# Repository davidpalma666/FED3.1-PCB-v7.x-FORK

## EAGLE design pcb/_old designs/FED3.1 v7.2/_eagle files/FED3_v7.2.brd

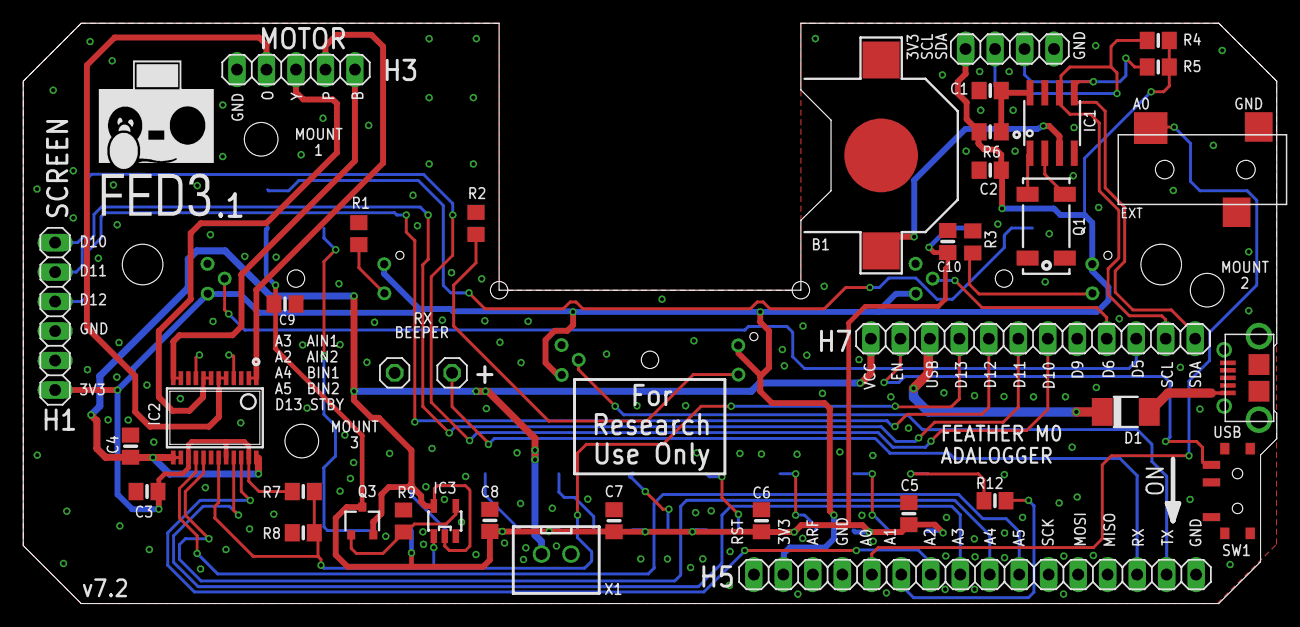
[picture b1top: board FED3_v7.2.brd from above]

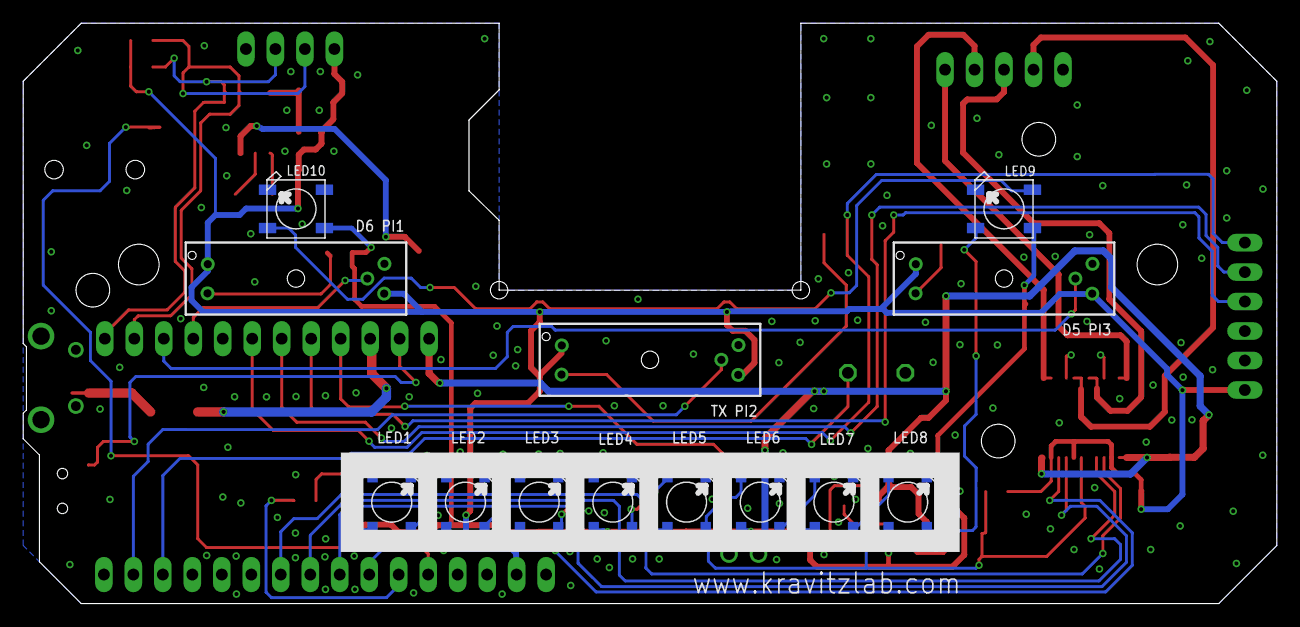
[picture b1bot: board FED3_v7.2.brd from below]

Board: 2 copper layers, 108.0 x 50.0 mm, 51 parts (13 on the bottom side), 45 nets.

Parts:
AUX_I2C: 1X04
B1: CR1220
BEEP1, BEEP2: 1X01
C1, C2, C5, C6, C7, C8, C9, C10: 10uF; 0805-NO
C3, C4: 10µF; 0805-NO
D1: DO-214AC
EXT: 35RASMT2BHNTRX
FEATHER_L: 1X16
FEATHER_R: 1X12
IC1: RTC_PCF8523T; SOIC8_150MIL
IC2: TB6612 SSOP; SSOP24
IC3: M74VHC1GT50DTT1G; SOT23-5
LED1, LED2, LED3, LED4, LED5, LED6, LED7, LED8, LED9, LED10: WS2812B5050; WS2812B
MOTOR: 1X05
PI1, PI2, PI3: GP1A57HR
Q1: 32.768; CRYSTAL_8X3.8
Q3: TSMT3
R1, R2, R3: 1k; R0805
R4, R5: 4K7; 0805-NO
R6: 1K; 0805-NO
R7: DNI; 0805-NO
R8: 4k7; 0805-NO
R9: 37k; R0805
R12: 470; 0805-NO
SCREEN: 1X06
SW1: SSSS811101
USB: USB_MICRO_B; ZX62D-B-5P8
X1: B2B-PH-K-S(LF)(SN); JST-XH-02-PACKAGE-ROUND-PAD

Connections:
3V3: AUX_I2C.1, C2.1, C3.1, FEATHER_L.2, IC2.15, IC2.20, IC2.23, PI1.1, PI1.3, PI2.1, PI2.3, PI3.1, PI3.3, R4.1, R5.2, R6.1, R7.2, SCREEN.6
A0: EXT.4, FEATHER_L.5
A1: FEATHER_L.6, R12.2
A2: FEATHER_L.7, IC2.22
A3: FEATHER_L.8, IC2.21
A4: FEATHER_L.9, IC2.17
A5: FEATHER_L.10, IC2.16
BLUE: IC2.11, IC2.12, MOTOR.5
D5: FEATHER_R.10, PI3.4
D6: FEATHER_R.9, PI1.4
D10: FEATHER_R.7, SCREEN.1
D11: FEATHER_R.6, SCREEN.2
D12: FEATHER_R.5, SCREEN.3
D13: FEATHER_R.4, IC2.19, IC3.1, R7.1, R8.2
EN: FEATHER_R.2, SW1.3
GND: AUX_I2C.4, B1.-, BEEP2.1, C1.2, C2.2, C3.2, C4.2, C5.2, C6.2, C7.2, C8.2, C9.2, C10.2, EXT.5, FEATHER_L.4, FEATHER_L.16, IC1.4, IC2.3, IC2.4, IC2.9, IC2.10, IC2.18, IC3.3, LED1.3-GND, LED2.3-GND, LED3.3-GND, LED4.3-GND, LED5.3-GND, LED6.3-GND, LED7.3-GND, LED8.3-GND, LED9.3-GND, LED10.3-GND, MOTOR.1, PI1.5, PI2.5, PI3.5, R1.2, R2.2, R3.2, R8.1, R9.1, SCREEN.4, SW1.2, USB.P$5, X1.1
unnamed: PI2.2, R2.1
unnamed: PI3.2, R1.1
unnamed: PI1.2, R3.1
unnamed: D1.A, USB.P$1
unnamed: LED1.2-DOUT, LED2.4-DIN
unnamed: C1.1, IC1.8, R6.2
unnamed: LED2.2-DOUT, LED3.4-DIN
unnamed: LED3.2-DOUT, LED4.4-DIN
unnamed: LED4.2-DOUT, LED5.4-DIN
unnamed: LED5.2-DOUT, LED6.4-DIN
unnamed: LED6.2-DOUT, LED7.4-DIN
unnamed: LED7.2-DOUT, LED8.4-DIN
unnamed: IC1.1, Q1.P$1
unnamed: IC1.2, Q1.P$4
unnamed: LED1.4-DIN, R12.1
unnamed: LED9.2-DOUT, LED10.4-DIN
unnamed: LED8.2-DOUT, LED9.4-DIN
ORANGE: IC2.5, IC2.6, MOTOR.2
OUT3: IC3.4, Q3.P$1, R9.2
PINK: IC2.1, IC2.2, MOTOR.4
RX: BEEP1.1, FEATHER_L.14
SCL: AUX_I2C.2, FEATHER_R.11, IC1.6, R4.2
SDA: AUX_I2C.3, FEATHER_R.12, IC1.5, R5.1
TX: FEATHER_L.15, PI2.4
USB: D1.C, FEATHER_R.3
VBAT1: B1.+$1, IC1.3
VCC: C4.1, FEATHER_R.1, IC2.13, IC2.14, IC2.24, IC3.2, IC3.5, Q3.P$2, X1.2
VCCNEO: C5.1, C6.1, C7.1, C8.1, C9.1, C10.1, LED1.1-VDD, LED2.1-VDD, LED3.1-VDD, LED4.1-VDD, LED5.1-VDD, LED6.1-VDD, LED7.1-VDD, LED8.1-VDD, LED9.1-VDD, LED10.1-VDD, Q3.P$3
YELLOW: IC2.7, IC2.8, MOTOR.3

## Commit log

2025-05-26 FED3_v7.3-REV.A
2025-05-26 older version 7.2
2025-05-29 project folders reorganized
2025-05-29 FED3 v7.4 - 1st step finished to review
    - U2 MPN & OEPSPN changed
    - X2 case corrected
    - USB D+ & D- corrected on USB-plug
    - manufacturer & BOM files still missing
2025-06-03 review step 2
    Realocação de labels e refªs:
    - sem qq alteração no circuito
    - alteração na PCB apenas a ver com alocação de Designators/SilkScreen parts
2025-06-04 buzzer step model updated
2025-06-05 get tunning with main branch
2025-06-06 v.7.4 - alterações rail power
    v.7.4
    - modificada estrutura rail power: VUSB apenas para Vcharging
    - modificadas Rs de LEDs para diminuir I
2025-06-06 re-arrumada folder structure
2025-06-09 v.7.4 - commit to final review
    - I2C plug moved to board front side
    - Rs to LEDs changed - impose less I
2025-06-11 FED3 v7.3 - 2nd revision
2025-06-12 modificados valores R14 R20: 2k2
2025-06-12 R20 off; R14=2k2
2025-06-25 gerados Gerbers&Drills
2025-06-25 BOM & Pick&Place
2025-06-25 retomar sincronia PCB com main-branch @12Junho
2025-06-25 adicionados ficheiros de produção
    - Gerbers & Drills
    - Pick & Place
    - BOM
2025-06-26 actualizados ficheiros produção
    - modificadas props de componentes para agilizar o criar ficheiros de produção
2025-07-03 getting tunned with Jonathan review #13
2025-07-03 last tunnings
    - Top & Bottom Fabrication Layers tuned
    - generated Gerbers&Drills files
    - generated P&P & BOM files
2025-07-07 'ultima versão revista; não em tunning com a versão oficial /Kravitz/FED3
2025-07-31 FED3 v.7.5
    - nova ficha USB C
    - andar carregador da pilha passa para capacidade carga 780mA
2025-08-01 FED3 v.7.5 - 1ºs ficheiros de progução
    - adicionada header para opção VTherm = Vbat
    - optimização para BOM: variedade-vs-quantidade
    - optimização de power-planes
    - gerados ficheiros produção para 1ª avaliação; há lá erros reconhecidos
2025-08-01 FED3 v.7.5 - 2ºs ficheiros produção
    - corrigidas posições de silks de alguns componentes
    - modificados Denominators de alguns componentes
2025-08-26 sincronia com a v.7.6 em produção
2025-08-26 Revert "sincronia com a v.7.6 em produção"
    This reverts commit 4ea7ff216a6da1369a32485a5f5775c3091efbbe.
2025-08-26 Reapply "sincronia com a v.7.6 em produção"
    This reverts commit 366851c8e0f049044401f28871b7d8940161753b.
2025-10-15 em tunning com main-branch
2025-10-29 adicionada folder de \_fw ao commited
2025-10-30 adicionadas notas _FED3.1 notes.txt
2025-12-12 PUp de Battery Charge
    - modificado valor R18 - R para setup de I Batt charge
    - actualizada PCB & BOM
2026-02-04 adicionadas placas para teste de FED3
    . "FED tester" - projecto com circuito de teste & PCB ainda não finalizada
    . "FED3 tester base - support"- projecto sem circuito; PCB para questão mecânica de fixação & alihamento agulhas:
    . "FED3 tester 1st production aux" - projecto com base do "FED tester" mas sem componentes: para 1ºs testes mecânicos
2026-02-04 alteração no nome do projecto "FED3 tester - support"
    . gerados novos Gerbers & Drill & .d356
2026-02-12 FED3 Tester - 1º routing finalizado
2026-02-20 FED3-tester
    - 'final' - antes de revisão com o Filipe
2026-03-05 FED 3 tester - actualizados novos OEPSPN & MPN; ainda 1 em falta
2026-04-15 final tunning??
    - fields de componentes actualizados
    - trocada polaridade na ficha botão de emergência
2026-04-23 tunning com v.7.7
2026-04-24 início FED3 tester - rev.B
2026-04-29 FED3 tester project
    .commit para sincronia
    .ainda longe do final
2026-05-04 FED3 tester - sync of the week
2026-05-06 FED3 tester rev.B & FED3 tester support rev.B
    -rev.B para 1ª revisão do Filipe
2026-05-07 adicionadas stitching-vias a planos GND
    nota:
    - não tem plano GND no top-layer, pq o attach-to-pads é sempre feito a 0.5mm independentemente do setup q se faça no plano;
    (algo já reportado com Kicad-bug em v10.0)
    - haveria situações em q entrava em conflito com pitch de componentes; tamanho de pads etc
2026-05-11 State LED - modificada côr para amarelo
2026-05-14 completos OEPSPN & MPN
    - andar de I-measure ZXCT1086 redimensionado
2026-05-14 revistos OEPSPN & MPN com gsheet - OK
2026-05-14 corrigidas distâncias Labels-&-Botões
2026-05-15 criado repo para boards de tester; tiradas deste projecto

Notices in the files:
parts and their libraries:
microbuilder: This work is placed in the public domain, and may be freely used for commercial and non-commercial work with the following conditions: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
